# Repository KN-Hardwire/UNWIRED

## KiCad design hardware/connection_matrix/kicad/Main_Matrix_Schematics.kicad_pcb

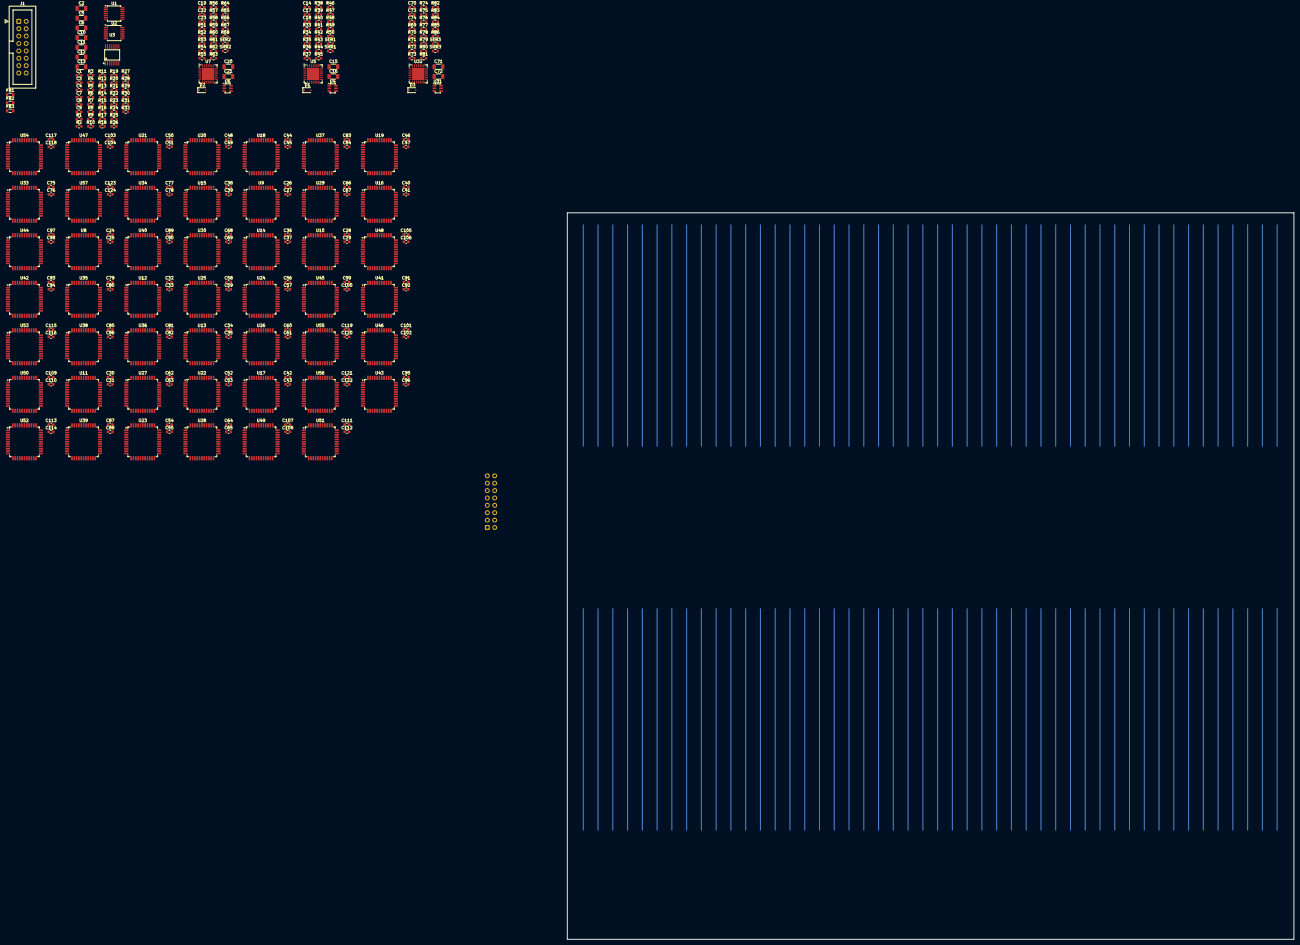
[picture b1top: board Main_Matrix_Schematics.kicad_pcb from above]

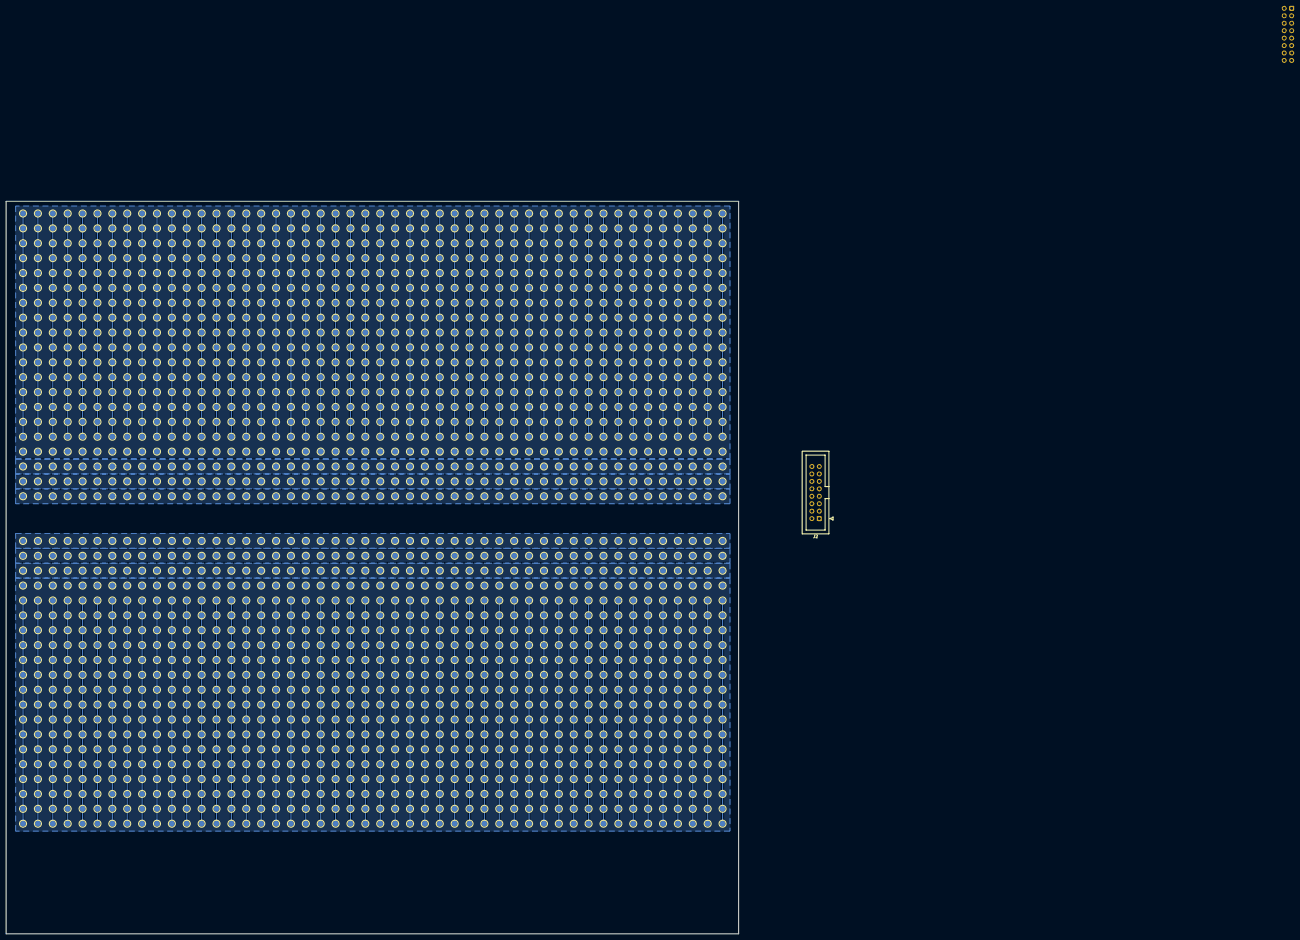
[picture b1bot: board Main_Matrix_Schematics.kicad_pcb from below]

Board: 4 copper layers, 250.0 x 250.0 mm, 2201 parts (1921 on the bottom side), 265 nets.

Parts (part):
+5P1, +5P1#2, +5P2, +5P2#2, +5P3, +5P3#2, +5P4, +5P4#2, +5P5, +5P5#2, +5P6, +5P6#2, +5P7, +5P7#2, +5P8, +5P8#2, +5P9, +5P9#2, +5P10, +5P10#2, +5P11, +5P11#2, +5P12, +5P12#2, +5P13, +5P13#2, +5P14, +5P14#2, +5P15, +5P15#2, +5P16, +5P16#2, +5P17, +5P17#2, +5P18, +5P18#2, +5P19, +5P19#2, +5P20, +5P20#2, +5P21, +5P21#2, +5P22, +5P22#2, +5P23, +5P23#2, +5P24, +5P24#2, +5P25, +5P25#2, +5P26, +5P26#2, +5P27, +5P27#2, +5P28, +5P28#2, +5P29, +5P29#2, +5P30, +5P30#2, +5P31, +5P31#2, +5P32, +5P32#2, +5P33, +5P33#2, +5P34, +5P34#2, +5P35, +5P35#2, +5P36, +5P36#2, +5P37, +5P37#2, +5P38, +5P38#2, +5P39, +5P39#2, +5P40, +5P40#2, +5P41, +5P41#2, +5P42, +5P42#2, +5P43, +5P43#2, +5P44, +5P44#2, +5P45, +5P45#2, +5P46, +5P46#2, +5P47, +5P47#2, +5P48, +5P48#2, +12P1, +12P1#2, +12P2, +12P2#2, +12P3, +12P3#2, +12P4, +12P4#2, +12P5, +12P5#2, +12P6, +12P6#2, +12P7, +12P7#2, +12P8, +12P8#2, +12P9, +12P9#2, +12P10, +12P10#2, +12P11, +12P11#2, +12P12, +12P12#2, +12P13, +12P13#2, +12P14, +12P14#2, +12P15, +12P15#2, +12P16, +12P16#2, +12P17, +12P17#2, +12P18, +12P18#2, +12P19, +12P19#2, +12P20, +12P20#2, +12P21, +12P21#2, +12P22, +12P22#2, +12P23, +12P23#2, +12P24, +12P24#2, +12P25, +12P25#2, +12P26, +12P26#2, +12P27, +12P27#2, +12P28, +12P28#2, +12P29, +12P29#2, +12P30, +12P30#2, +12P31, +12P31#2, +12P32, +12P32#2, +12P33, +12P33#2, +12P34, +12P34#2, +12P35, +12P35#2, +12P36, +12P36#2, +12P37, +12P37#2, +12P38, +12P38#2, +12P39, +12P39#2, +12P40, +12P40#2, +12P41, +12P41#2, +12P42, +12P42#2, +12P43, +12P43#2, +12P44, +12P44#2, +12P45, +12P45#2, +12P46, +12P46#2, +12P47, +12P47#2, +12P48, +12P48#2: Module_Pad; TestPoint_Pad_D2.0mm
-12P1, -12P1#2, -12P2, -12P2#2, -12P3, -12P3#2, -12P4, -12P4#2, -12P5, -12P5#2, -12P6, -12P6#2, -12P7, -12P7#2, -12P8, -12P8#2, -12P9, -12P9#2, -12P10, -12P10#2, -12P11, -12P11#2, -12P12, -12P12#2, -12P13, -12P13#2, -12P14, -12P14#2, -12P15, -12P15#2, -12P16, -12P16#2, -12P17, -12P17#2, -12P18, -12P18#2, -12P19, -12P19#2, -12P20, -12P20#2, -12P21, -12P21#2, -12P22, -12P22#2, -12P23, -12P23#2, -12P24, -12P24#2, -12P25, -12P25#2, -12P26, -12P26#2, -12P27, -12P27#2, -12P28, -12P28#2, -12P29, -12P29#2, -12P30, -12P30#2, -12P31, -12P31#2, -12P32, -12P32#2, -12P33, -12P33#2, -12P34, -12P34#2, -12P35, -12P35#2, -12P36, -12P36#2, -12P37, -12P37#2, -12P38, -12P38#2, -12P39, -12P39#2, -12P40, -12P40#2, -12P41, -12P41#2, -12P42, -12P42#2, -12P43, -12P43#2, -12P44, -12P44#2, -12P45, -12P45#2, -12P46, -12P46#2, -12P47, -12P47#2, -12P48, -12P48#2: Module_Pad; TestPoint_Pad_D2.0mm
C1, C3, C4, C7, C8, C9, C14, C17, C18, C19, C22, C23, C70, C73, C74: 100nF; C_0603_1608Metric
C2, C5, C6, C10, C11, C12, C13, C15, C16, C20, C21, C71, C72: 10uF; C_1206_3216Metric
C24, C25, C26, C27, C28, C29, C30, C31, C32, C33, C34, C35, C36, C37, C38, C39, C40, C41, C42, C43, C44, C45, C46, C47, C48, C49, C50, C51, C52, C53, C54, C55, C56, C57, C58, C59, C60, C61, C62, C63, C64, C65, C66, C67, C68, C69, C75, C76, C77, C78, C79, C80, C81, C82, C83, C84, C85, C86, C87, C88, C89, C90, C91, C92, C93, C94, C95, C96, C97, C98, C99, C100, C101, C102, C103, C104, C105, C106, C107, C108, C109, C110, C111, C112, C113, C114, C115, C116, C117, C118, C119, C120, C121, C122, C123, C124: 100n; C_0603_1608Metric
D1, D2, D3: BAT54J; D_SOD-323F
FB1, FB2, FB3: FerriteBead; L_0805_2012Metric
GNDP1, GNDP1#2, GNDP2, GNDP2#2, GNDP3, GNDP3#2, GNDP4, GNDP4#2, GNDP5, GNDP5#2, GNDP6, GNDP6#2, GNDP7, GNDP7#2, GNDP8, GNDP8#2, GNDP9, GNDP9#2, GNDP10, GNDP10#2, GNDP11, GNDP11#2, GNDP12, GNDP12#2, GNDP13, GNDP13#2, GNDP14, GNDP14#2, GNDP15, GNDP15#2, GNDP16, GNDP16#2, GNDP17, GNDP17#2, GNDP18, GNDP18#2, GNDP19, GNDP19#2, GNDP20, GNDP20#2, GNDP21, GNDP21#2, GNDP22, GNDP22#2, GNDP23, GNDP23#2, GNDP24, GNDP24#2, GNDP25, GNDP25#2, GNDP26, GNDP26#2, GNDP27, GNDP27#2, GNDP28, GNDP28#2, GNDP29, GNDP29#2, GNDP30, GNDP30#2, GNDP31, GNDP31#2, GNDP32, GNDP32#2, GNDP33, GNDP33#2, GNDP34, GNDP34#2, GNDP35, GNDP35#2, GNDP36, GNDP36#2, GNDP37, GNDP37#2, GNDP38, GNDP38#2, GNDP39, GNDP39#2, GNDP40, GNDP40#2, GNDP41, GNDP41#2, GNDP42, GNDP42#2, GNDP43, GNDP43#2, GNDP44, GNDP44#2, GNDP45, GNDP45#2, GNDP46, GNDP46#2, GNDP47, GNDP47#2, GNDP48, GNDP48#2: Module_Pad; TestPoint_Pad_D2.0mm
J1, J2: Conn_02x08_Odd_Even; IDC-Header_2x08_P2.54mm_Vertical
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
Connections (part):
+5V: C1.2, C2.1, C11.1, C14.1, C15.1, C17.1, C18.1, C19.1, C20.1, C22.1, C23.1, C24.2, C26.2, C28.2, C30.2, C32.2, C34.2, C36.2, C38.2, C40.2, C42.2, C44.2, C46.2, C48.2, C50.2, C52.2, C54.2, C56.2, C58.2, C60.2, C62.2, C64.2, C66.2, C68.2, C70.1, C71.1, C73.1, C74.1, C75.2, C77.2, C79.2, C81.2, C83.2, C85.2, C87.2, C89.2, C91.2, C93.2, C95.2, C97.2, C99.2, C101.2, C103.2, C105.2, C107.2, C109.2, C111.2, C113.2, C115.2, C117.2, C119.2, C121.2, C123.2, FB1.2, J1.5, SER1.1, SER2.1, SER3.1, U3.3 (AVDD), U3.9 (~CLR), U4.5 (VCC), U5.5 (V_{DD}), U6.5 (VCC), U7.5 (V_{DD}), U7.11 (A0), U8.38 (VDD), U9.38 (VDD), U10.38 (VDD), U11.38 (VDD), U12.38 (VDD)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
+12V: C3.2, C5.1, C7.1, C8.1, C10.1, FB2.2, J1.1, U1.4 (V+), U2.4 (V+)
-5V: C13.1, C16.1, C21.1, C25.2, C27.2, C29.2, C31.2, C33.2, C35.2, C37.2, C39.2, C41.2, C43.2, C45.2, C47.2, C49.2, C51.2, C53.2, C55.2, C57.2, C59.2, C61.2, C63.2, C65.2, C67.2, C69.2, C72.1, C76.2, C78.2, C80.2, C82.2, C84.2, C86.2, C88.2, C90.2, C92.2, C94.2, C96.2, C98.2, C100.2, C102.2, C104.2, C106.2, C108.2, C110.2, C112.2, C114.2, C116.2, C118.2, C120.2, C122.2, C124.2, J1.7, U8.16 (VEE), U9.16 (VEE), U10.16 (VEE), U11.16 (VEE), U12.16 (VEE), U13.16 (VEE), U14.16 (VEE), U15.16 (VEE), U16.16 (VEE), U17.16 (VEE), U18.16 (VEE), U19.16 (VEE), U20.16 (VEE), U21.16 (VEE), U22.16 (VEE), U23.16 (VEE), U24.16 (VEE), U25.16 (VEE), U26.16 (VEE), U27.16 (VEE), U28.16 (VEE), U29.16 (VEE), U30.16 (VEE), U33.16 (VEE), U34.16 (VEE), U35.16 (VEE), U36.16 (VEE)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
-12V: C4.2, C6.1, C7.2, C8.2, C12.1, FB3.1, J1.3, U1.11 (V-), U2.11 (V-)
/+5_OUT: +5P1.1 (1_1), +5P1#2.1 (1_1), +5P2.1 (1_1), +5P2#2.1 (1_1), +5P3.1 (1_1), +5P3#2.1 (1_1), +5P4.1 (1_1), +5P4#2.1 (1_1), +5P5.1 (1_1), +5P5#2.1 (1_1), +5P6.1 (1_1), +5P6#2.1 (1_1), +5P7.1 (1_1), +5P7#2.1 (1_1), +5P8.1 (1_1), +5P8#2.1 (1_1), +5P9.1 (1_1), +5P9#2.1 (1_1), +5P10.1 (1_1), +5P10#2.1 (1_1), +5P11.1 (1_1), +5P11#2.1 (1_1), +5P12.1 (1_1), +5P12#2.1 (1_1), +5P13.1 (1_1), +5P13#2.1 (1_1), +5P14.1 (1_1), +5P14#2.1 (1_1), +5P15.1 (1_1), +5P15#2.1 (1_1), +5P16.1 (1_1), +5P16#2.1 (1_1), +5P17.1 (1_1), +5P17#2.1 (1_1), +5P18.1 (1_1), +5P18#2.1 (1_1), +5P19.1 (1_1), +5P19#2.1 (1_1), +5P20.1 (1_1), +5P20#2.1 (1_1), +5P21.1 (1_1), +5P21#2.1 (1_1), +5P22.1 (1_1), +5P22#2.1 (1_1), +5P23.1 (1_1), +5P23#2.1 (1_1), +5P24.1 (1_1), +5P24#2.1 (1_1), +5P25.1 (1_1), +5P25#2.1 (1_1), +5P26.1 (1_1), +5P26#2.1 (1_1), +5P27.1 (1_1), +5P27#2.1 (1_1), +5P28.1 (1_1), +5P28#2.1 (1_1), +5P29.1 (1_1), +5P29#2.1 (1_1), +5P30.1 (1_1), +5P30#2.1 (1_1), +5P31.1 (1_1), +5P31#2.1 (1_1), +5P32.1 (1_1), +5P32#2.1 (1_1), +5P33.1 (1_1), +5P33#2.1 (1_1), +5P34.1 (1_1), +5P34#2.1 (1_1), +5P35.1 (1_1), +5P35#2.1 (1_1), +5P36.1 (1_1), +5P36#2.1 (1_1), +5P37.1 (1_1), +5P37#2.1 (1_1), +5P38.1 (1_1), +5P38#2.1 (1_1), +5P39.1 (1_1), +5P39#2.1 (1_1), +5P40.1 (1_1), +5P40#2.1 (1_1)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
/+12_OUT: +12P1.1 (1_1), +12P1#2.1 (1_1), +12P2.1 (1_1), +12P2#2.1 (1_1), +12P3.1 (1_1), +12P3#2.1 (1_1), +12P4.1 (1_1), +12P4#2.1 (1_1), +12P5.1 (1_1), +12P5#2.1 (1_1), +12P6.1 (1_1), +12P6#2.1 (1_1), +12P7.1 (1_1), +12P7#2.1 (1_1), +12P8.1 (1_1), +12P8#2.1 (1_1), +12P9.1 (1_1), +12P9#2.1 (1_1), +12P10.1 (1_1), +12P10#2.1 (1_1), +12P11.1 (1_1), +12P11#2.1 (1_1), +12P12.1 (1_1), +12P12#2.1 (1_1), +12P13.1 (1_1), +12P13#2.1 (1_1), +12P14.1 (1_1), +12P14#2.1 (1_1), +12P15.1 (1_1), +12P15#2.1 (1_1), +12P16.1 (1_1), +12P16#2.1 (1_1), +12P17.1 (1_1), +12P17#2.1 (1_1), +12P18.1 (1_1), +12P18#2.1 (1_1), +12P19.1 (1_1), +12P19#2.1 (1_1), +12P20.1 (1_1), +12P20#2.1 (1_1), +12P21.1 (1_1), +12P21#2.1 (1_1), +12P22.1 (1_1), +12P22#2.1 (1_1), +12P23.1 (1_1), +12P23#2.1 (1_1), +12P24.1 (1_1), +12P24#2.1 (1_1), +12P25.1 (1_1), +12P25#2.1 (1_1), +12P26.1 (1_1), +12P26#2.1 (1_1), +12P27.1 (1_1), +12P27#2.1 (1_1), +12P28.1 (1_1), +12P28#2.1 (1_1), +12P29.1 (1_1), +12P29#2.1 (1_1), +12P30.1 (1_1), +12P30#2.1 (1_1), +12P31.1 (1_1), +12P31#2.1 (1_1), +12P32.1 (1_1), +12P32#2.1 (1_1), +12P33.1 (1_1), +12P33#2.1 (1_1), +12P34.1 (1_1), +12P34#2.1 (1_1), +12P35.1 (1_1), +12P35#2.1 (1_1), +12P36.1 (1_1), +12P36#2.1 (1_1), +12P37.1 (1_1), +12P37#2.1 (1_1), +12P38.1 (1_1), +12P38#2.1 (1_1), +12P39.1 (1_1), +12P39#2.1 (1_1), +12P40.1 (1_1), +12P40#2.1 (1_1)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
/-12_OUT: -12P1.1 (1_1), -12P1#2.1 (1_1), -12P2.1 (1_1), -12P2#2.1 (1_1), -12P3.1 (1_1), -12P3#2.1 (1_1), -12P4.1 (1_1), -12P4#2.1 (1_1), -12P5.1 (1_1), -12P5#2.1 (1_1), -12P6.1 (1_1), -12P6#2.1 (1_1), -12P7.1 (1_1), -12P7#2.1 (1_1), -12P8.1 (1_1), -12P8#2.1 (1_1), -12P9.1 (1_1), -12P9#2.1 (1_1), -12P10.1 (1_1), -12P10#2.1 (1_1), -12P11.1 (1_1), -12P11#2.1 (1_1), -12P12.1 (1_1), -12P12#2.1 (1_1), -12P13.1 (1_1), -12P13#2.1 (1_1), -12P14.1 (1_1), -12P14#2.1 (1_1), -12P15.1 (1_1), -12P15#2.1 (1_1), -12P16.1 (1_1), -12P16#2.1 (1_1), -12P17.1 (1_1), -12P17#2.1 (1_1), -12P18.1 (1_1), -12P18#2.1 (1_1), -12P19.1 (1_1), -12P19#2.1 (1_1), -12P20.1 (1_1), -12P20#2.1 (1_1), -12P21.1 (1_1), -12P21#2.1 (1_1), -12P22.1 (1_1), -12P22#2.1 (1_1), -12P23.1 (1_1), -12P23#2.1 (1_1), -12P24.1 (1_1), -12P24#2.1 (1_1), -12P25.1 (1_1), -12P25#2.1 (1_1), -12P26.1 (1_1), -12P26#2.1 (1_1), -12P27.1 (1_1), -12P27#2.1 (1_1), -12P28.1 (1_1), -12P28#2.1 (1_1), -12P29.1 (1_1), -12P29#2.1 (1_1), -12P30.1 (1_1), -12P30#2.1 (1_1), -12P31.1 (1_1), -12P31#2.1 (1_1), -12P32.1 (1_1), -12P32#2.1 (1_1), -12P33.1 (1_1), -12P33#2.1 (1_1), -12P34.1 (1_1), -12P34#2.1 (1_1), -12P35.1 (1_1), -12P35#2.1 (1_1), -12P36.1 (1_1), -12P36#2.1 (1_1), -12P37.1 (1_1), -12P37#2.1 (1_1), -12P38.1 (1_1), -12P38#2.1 (1_1), -12P39.1 (1_1), -12P39#2.1 (1_1), -12P40.1 (1_1), -12P40#2.1 (1_1)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
/AUX_BUS0: R7.2, U27.31 (X0), U28.31 (X0), U29.31 (X0), U30.31 (X0), U37.31 (X0), U38.31 (X0), U39.31 (X0), U40.31 (X0), U53.31 (X0), U54.31 (X0), U55.31 (X0), U56.31 (X0)
/AUX_BUS1: R8.2, U27.30 (X1), U28.30 (X1), U29.30 (X1), U30.30 (X1), U37.30 (X1), U38.30 (X1), U39.30 (X1), U40.30 (X1), U53.30 (X1), U54.30 (X1), U55.30 (X1), U56.30 (X1)
/AUX_BUS2: R15.2, U27.29 (X2), U28.29 (X2), U29.29 (X2), U30.29 (X2), U37.29 (X2), U38.29 (X2), U39.29 (X2), U40.29 (X2), U53.29 (X2), U54.29 (X2), U55.29 (X2), U56.29 (X2)
/AUX_BUS3: R16.2, U27.28 (X3), U28.28 (X3), U29.28 (X3), U30.28 (X3), U37.28 (X3), U38.28 (X3), U39.28 (X3), U40.28 (X3), U53.28 (X3), U54.28 (X3), U55.28 (X3), U56.28 (X3)
/AUX_BUS4: R23.2, U27.27 (X4), U28.27 (X4), U29.27 (X4), U30.27 (X4), U37.27 (X4), U38.27 (X4), U39.27 (X4), U40.27 (X4), U53.27 (X4), U54.27 (X4), U55.27 (X4), U56.27 (X4)
/AUX_BUS5: R24.2, U27.26 (X5), U28.26 (X5), U29.26 (X5), U30.26 (X5), U37.26 (X5), U38.26 (X5), U39.26 (X5), U40.26 (X5), U53.26 (X5), U54.26 (X5), U55.26 (X5), U56.26 (X5)
/AUX_BUS6: R31.2, U27.3 (X6), U28.3 (X6), U29.3 (X6), U30.3 (X6), U37.3 (X6), U38.3 (X6), U39.3 (X6), U40.3 (X6), U53.3 (X6), U54.3 (X6), U55.3 (X6), U56.3 (X6)
/AUX_BUS7: R32.2, U27.4 (X7), U28.4 (X7), U29.4 (X7), U30.4 (X7), U37.4 (X7), U38.4 (X7), U39.4 (X7), U40.4 (X7), U53.4 (X7), U54.4 (X7), U55.4 (X7), U56.4 (X7)
/AUX_BUS8: J2.1, U27.5 (X8), U28.5 (X8), U29.5 (X8), U30.5 (X8), U37.5 (X8), U38.5 (X8), U39.5 (X8), U40.5 (X8), U53.5 (X8), U54.5 (X8), U55.5 (X8), U56.5 (X8)
/AUX_BUS9: J2.3, U27.6 (X9), U28.6 (X9), U29.6 (X9), U30.6 (X9), U37.6 (X9), U38.6 (X9), U39.6 (X9), U40.6 (X9), U53.6 (X9), U54.6 (X9), U55.6 (X9), U56.6 (X9)
/AUX_BUS10: J2.5, U27.7 (X10), U28.7 (X10), U29.7 (X10), U30.7 (X10), U37.7 (X10), U38.7 (X10), U39.7 (X10), U40.7 (X10), U53.7 (X10), U54.7 (X10), U55.7 (X10), U56.7 (X10)
/AUX_BUS11: J2.7, U27.8 (X11), U28.8 (X11), U29.8 (X11), U30.8 (X11), U37.8 (X11), U38.8 (X11), U39.8 (X11), U40.8 (X11), U53.8 (X11), U54.8 (X11), U55.8 (X11), U56.8 (X11)
/AUX_BUS12: J2.9, U27.25 (X12), U28.25 (X12), U29.25 (X12), U30.25 (X12), U37.25 (X12), U38.25 (X12), U39.25 (X12), U40.25 (X12), U53.25 (X12), U54.25 (X12), U55.25 (X12), U56.25 (X12)
/AUX_BUS13: J2.11, U27.24 (X13), U28.24 (X13), U29.24 (X13), U30.24 (X13), U37.24 (X13), U38.24 (X13), U39.24 (X13), U40.24 (X13), U53.24 (X13), U54.24 (X13), U55.24 (X13), U56.24 (X13)
/AUX_BUS14: J2.13, U27.1 (X14), U28.1 (X14), U29.1 (X14), U30.1 (X14), U37.1 (X14), U38.1 (X14), U39.1 (X14), U40.1 (X14), U53.1 (X14), U54.1 (X14), U55.1 (X14), U56.1 (X14)
/AUX_BUS15: J2.15, U27.2 (X15), U28.2 (X15), U29.2 (X15), U30.2 (X15), U37.2 (X15), U38.2 (X15), U39.2 (X15), U40.2 (X15), U53.2 (X15), U54.2 (X15), U55.2 (X15), U56.2 (X15)
/DAC_A: U1.3 (+), U3.4 (VOUTA)
/DAC_B: U1.5 (+), U3.13 (VOUTB)
/DAC_C: U1.10 (+), U3.5 (VOUTC)
/DAC_D: U1.12 (+), U3.12 (VOUTD)
/DAC_E: U2.3 (+), U3.6 (VOUTE)
/DAC_F: U2.5 (+), U3.11 (VOUTF)
/DAC_G: U2.10 (+), U3.7 (VOUTG)
/DAC_H: U2.12 (+), U3.10 (VOUTH)
/SPI.CS1: J1.9, U5.7 (~CS), U7.7 (~CS), U32.7 (~CS)
/SPI.CS2: J1.10, U3.2 (~SYNC)
/SPI.MOSI: J1.13, U3.15 (DIN), U5.9 (SI), U7.9 (SI), U32.9 (SI)
/SPI.SCK: J1.11, U3.16 (SCLK), U5.8 (SCK), U7.8 (SCK), U32.8 (SCK)
/Sector1/CBUS10: U8.31 (X0), U11.31 (X0), U12.31 (X0), U15.31 (X0), U16.31 (X0), U23.31 (X0), U24.31 (X0), U45.31 (X0), U46.31 (X0), U49.31 (X0), U50.31 (X0), U57.31 (X0)
/Sector1/CBUS11: U8.30 (X1), U11.30 (X1), U12.30 (X1), U15.30 (X1), U16.30 (X1), U23.30 (X1), U24.30 (X1), U45.30 (X1), U46.30 (X1), U49.30 (X1), U50.30 (X1), U57.30 (X1)
/Sector1/CBUS12: U8.29 (X2), U11.29 (X2), U12.29 (X2), U15.29 (X2), U16.29 (X2), U23.29 (X2), U24.29 (X2), U45.29 (X2), U46.29 (X2), U49.29 (X2), U50.29 (X2), U57.29 (X2)
/Sector1/CBUS13: U8.28 (X3), U11.28 (X3), U12.28 (X3), U15.28 (X3), U16.28 (X3), U23.28 (X3), U24.28 (X3), U45.28 (X3), U46.28 (X3), U49.28 (X3), U50.28 (X3), U57.28 (X3)
/Sector1/CBUS14: U8.27 (X4), U11.27 (X4), U12.27 (X4), U15.27 (X4), U16.27 (X4), U23.27 (X4), U24.27 (X4), U45.27 (X4), U46.27 (X4), U49.27 (X4), U50.27 (X4), U57.27 (X4)
/Sector1/CBUS15: U8.26 (X5), U11.26 (X5), U12.26 (X5), U15.26 (X5), U16.26 (X5), U23.26 (X5), U24.26 (X5), U45.26 (X5), U46.26 (X5), U49.26 (X5), U50.26 (X5), U57.26 (X5)
/Sector1/CBUS16: U8.3 (X6), U11.3 (X6), U12.3 (X6), U15.3 (X6), U16.3 (X6), U23.3 (X6), U24.3 (X6), U45.3 (X6), U46.3 (X6), U49.3 (X6), U50.3 (X6), U57.3 (X6)
/Sector1/CBUS17: U8.4 (X7), U11.4 (X7), U12.4 (X7), U15.4 (X7), U16.4 (X7), U23.4 (X7), U24.4 (X7), U45.4 (X7), U46.4 (X7), U49.4 (X7), U50.4 (X7), U57.4 (X7)
/Sector1/CBUS18: U8.5 (X8), U11.5 (X8), U12.5 (X8), U15.5 (X8), U16.5 (X8), U23.5 (X8), U24.5 (X8), U45.5 (X8), U46.5 (X8), U49.5 (X8), U50.5 (X8), U57.5 (X8)
/Sector1/CBUS19: U8.6 (X9), U11.6 (X9), U12.6 (X9), U15.6 (X9), U16.6 (X9), U23.6 (X9), U24.6 (X9), U45.6 (X9), U46.6 (X9), U49.6 (X9), U50.6 (X9), U57.6 (X9)
/Sector1/CBUS20: U13.31 (X0), U14.31 (X0), U18.31 (X0), U19.31 (X0), U20.31 (X0), U21.31 (X0), U22.31 (X0), U25.31 (X0), U43.31 (X0), U44.31 (X0), U48.31 (X0), U51.31 (X0)
/Sector1/CBUS21: U13.30 (X1), U14.30 (X1), U18.30 (X1), U19.30 (X1), U20.30 (X1), U21.30 (X1), U22.30 (X1), U25.30 (X1), U43.30 (X1), U44.30 (X1), U48.30 (X1), U51.30 (X1)
/Sector1/CBUS22: U13.29 (X2), U14.29 (X2), U18.29 (X2), U19.29 (X2), U20.29 (X2), U21.29 (X2), U22.29 (X2), U25.29 (X2), U43.29 (X2), U44.29 (X2), U48.29 (X2), U51.29 (X2)
/Sector1/CBUS23: U13.28 (X3), U14.28 (X3), U18.28 (X3), U19.28 (X3), U20.28 (X3), U21.28 (X3), U22.28 (X3), U25.28 (X3), U43.28 (X3), U44.28 (X3), U48.28 (X3), U51.28 (X3)
/Sector1/CBUS24: U13.27 (X4), U14.27 (X4), U18.27 (X4), U19.27 (X4), U20.27 (X4), U21.27 (X4), U22.27 (X4), U25.27 (X4), U43.27 (X4), U44.27 (X4), U48.27 (X4), U51.27 (X4)
/Sector1/CBUS25: U13.26 (X5), U14.26 (X5), U18.26 (X5), U19.26 (X5), U20.26 (X5), U21.26 (X5), U22.26 (X5), U25.26 (X5), U43.26 (X5), U44.26 (X5), U48.26 (X5), U51.26 (X5)
/Sector1/CBUS26: U13.3 (X6), U14.3 (X6), U18.3 (X6), U19.3 (X6), U20.3 (X6), U21.3 (X6), U22.3 (X6), U25.3 (X6), U43.3 (X6), U44.3 (X6), U48.3 (X6), U51.3 (X6)
/Sector1/CBUS27: U13.4 (X7), U14.4 (X7), U18.4 (X7), U19.4 (X7), U20.4 (X7), U21.4 (X7), U22.4 (X7), U25.4 (X7), U43.4 (X7), U44.4 (X7), U48.4 (X7), U51.4 (X7)
/Sector1/CBUS28: U13.5 (X8), U14.5 (X8), U18.5 (X8), U19.5 (X8), U20.5 (X8), U21.5 (X8), U22.5 (X8), U25.5 (X8), U43.5 (X8), U44.5 (X8), U48.5 (X8), U51.5 (X8)
/Sector1/CBUS29: U13.6 (X9), U14.6 (X9), U18.6 (X9), U19.6 (X9), U20.6 (X9), U21.6 (X9), U22.6 (X9), U25.6 (X9), U43.6 (X9), U44.6 (X9), U48.6 (X9), U51.6 (X9)
/Sector1/CBUS30: U9.31 (X0), U10.31 (X0), U17.31 (X0), U26.31 (X0), U33.31 (X0), U34.31 (X0), U35.31 (X0), U36.31 (X0), U41.31 (X0), U42.31 (X0), U47.31 (X0), U52.31 (X0)
/Sector1/CBUS31: U9.30 (X1), U10.30 (X1), U17.30 (X1), U26.30 (X1), U33.30 (X1), U34.30 (X1), U35.30 (X1), U36.30 (X1), U41.30 (X1), U42.30 (X1), U47.30 (X1), U52.30 (X1)
/Sector1/CBUS32: U9.29 (X2), U10.29 (X2), U17.29 (X2), U26.29 (X2), U33.29 (X2), U34.29 (X2), U35.29 (X2), U36.29 (X2), U41.29 (X2), U42.29 (X2), U47.29 (X2), U52.29 (X2)
/Sector1/CBUS33: U9.28 (X3), U10.28 (X3), U17.28 (X3), U26.28 (X3), U33.28 (X3), U34.28 (X3), U35.28 (X3), U36.28 (X3), U41.28 (X3), U42.28 (X3), U47.28 (X3), U52.28 (X3)
/Sector1/CBUS34: U9.27 (X4), U10.27 (X4), U17.27 (X4), U26.27 (X4), U33.27 (X4), U34.27 (X4), U35.27 (X4), U36.27 (X4), U41.27 (X4), U42.27 (X4), U47.27 (X4), U52.27 (X4)
/Sector1/CBUS35: U9.26 (X5), U10.26 (X5), U17.26 (X5), U26.26 (X5), U33.26 (X5), U34.26 (X5), U35.26 (X5), U36.26 (X5), U41.26 (X5), U42.26 (X5), U47.26 (X5), U52.26 (X5)
/Sector1/CBUS36: U9.3 (X6), U10.3 (X6), U17.3 (X6), U26.3 (X6), U33.3 (X6), U34.3 (X6), U35.3 (X6), U36.3 (X6), U41.3 (X6), U42.3 (X6), U47.3 (X6), U52.3 (X6)
/Sector1/CBUS37: U9.4 (X7), U10.4 (X7), U17.4 (X7), U26.4 (X7), U33.4 (X7), U34.4 (X7), U35.4 (X7), U36.4 (X7), U41.4 (X7), U42.4 (X7), U47.4 (X7), U52.4 (X7)
/Sector1/CBUS38: U9.5 (X8), U10.5 (X8), U17.5 (X8), U26.5 (X8), U33.5 (X8), U34.5 (X8), U35.5 (X8), U36.5 (X8), U41.5 (X8), U42.5 (X8), U47.5 (X8), U52.5 (X8)
/Sector1/CBUS39: U9.6 (X9), U10.6 (X9), U17.6 (X9), U26.6 (X9), U33.6 (X9), U34.6 (X9), U35.6 (X9), U36.6 (X9), U41.6 (X9), U42.6 (X9), U47.6 (X9), U52.6 (X9)
/Sector1/CBUS110: U8.7 (X10), U11.7 (X10), U12.7 (X10), U15.7 (X10), U16.7 (X10), U23.7 (X10), U24.7 (X10), U45.7 (X10), U46.7 (X10), U49.7 (X10), U50.7 (X10), U57.7 (X10)
/Sector1/CBUS111: U8.8 (X11), U11.8 (X11), U12.8 (X11), U15.8 (X11), U16.8 (X11), U23.8 (X11), U24.8 (X11), U45.8 (X11), U46.8 (X11), U49.8 (X11), U50.8 (X11), U57.8 (X11)
/Sector1/CBUS112: U8.25 (X12), U11.25 (X12), U12.25 (X12), U15.25 (X12), U16.25 (X12), U23.25 (X12), U24.25 (X12), U45.25 (X12), U46.25 (X12), U49.25 (X12), U50.25 (X12), U57.25 (X12)
/Sector1/CBUS113: U8.24 (X13), U11.24 (X13), U12.24 (X13), U15.24 (X13), U16.24 (X13), U23.24 (X13), U24.24 (X13), U45.24 (X13), U46.24 (X13), U49.24 (X13), U50.24 (X13), U57.24 (X13)
/Sector1/CBUS114: U8.1 (X14), U11.1 (X14), U12.1 (X14), U15.1 (X14), U16.1 (X14), U23.1 (X14), U24.1 (X14), U45.1 (X14), U46.1 (X14), U49.1 (X14), U50.1 (X14), U57.1 (X14)
/Sector1/CBUS115: U8.2 (X15), U11.2 (X15), U12.2 (X15), U15.2 (X15), U16.2 (X15), U23.2 (X15), U24.2 (X15), U45.2 (X15), U46.2 (X15), U49.2 (X15), U50.2 (X15), U57.2 (X15)
/Sector1/CBUS210: U13.7 (X10), U14.7 (X10), U18.7 (X10), U19.7 (X10), U20.7 (X10), U21.7 (X10), U22.7 (X10), U25.7 (X10), U43.7 (X10), U44.7 (X10), U48.7 (X10), U51.7 (X10)
/Sector1/CBUS211: U13.8 (X11), U14.8 (X11), U18.8 (X11), U19.8 (X11), U20.8 (X11), U21.8 (X11), U22.8 (X11), U25.8 (X11), U43.8 (X11), U44.8 (X11), U48.8 (X11), U51.8 (X11)
/Sector1/CBUS212: U13.25 (X12), U14.25 (X12), U18.25 (X12), U19.25 (X12), U20.25 (X12), U21.25 (X12), U22.25 (X12), U25.25 (X12), U43.25 (X12), U44.25 (X12), U48.25 (X12), U51.25 (X12)
/Sector1/CBUS213: U13.24 (X13), U14.24 (X13), U18.24 (X13), U19.24 (X13), U20.24 (X13), U21.24 (X13), U22.24 (X13), U25.24 (X13), U43.24 (X13), U44.24 (X13), U48.24 (X13), U51.24 (X13)
/Sector1/CBUS214: U13.1 (X14), U14.1 (X14), U18.1 (X14), U19.1 (X14), U20.1 (X14), U21.1 (X14), U22.1 (X14), U25.1 (X14), U43.1 (X14), U44.1 (X14), U48.1 (X14), U51.1 (X14)
/Sector1/CBUS215: U13.2 (X15), U14.2 (X15), U18.2 (X15), U19.2 (X15), U20.2 (X15), U21.2 (X15), U22.2 (X15), U25.2 (X15), U43.2 (X15), U44.2 (X15), U48.2 (X15), U51.2 (X15)
/Sector1/CBUS310: U9.7 (X10), U10.7 (X10), U17.7 (X10), U26.7 (X10), U33.7 (X10), U34.7 (X10), U35.7 (X10), U36.7 (X10), U41.7 (X10), U42.7 (X10), U47.7 (X10), U52.7 (X10)
/Sector1/CBUS311: U9.8 (X11), U10.8 (X11), U17.8 (X11), U26.8 (X11), U33.8 (X11), U34.8 (X11), U35.8 (X11), U36.8 (X11), U41.8 (X11), U42.8 (X11), U47.8 (X11), U52.8 (X11)
/Sector1/CBUS312: U9.25 (X12), U10.25 (X12), U17.25 (X12), U26.25 (X12), U33.25 (X12), U34.25 (X12), U35.25 (X12), U36.25 (X12), U41.25 (X12), U42.25 (X12), U47.25 (X12), U52.25 (X12)
/Sector1/CBUS313: U9.24 (X13), U10.24 (X13), U17.24 (X13), U26.24 (X13), U33.24 (X13), U34.24 (X13), U35.24 (X13), U36.24 (X13), U41.24 (X13), U42.24 (X13), U47.24 (X13), U52.24 (X13)
/Sector1/CBUS314: U9.1 (X14), U10.1 (X14), U17.1 (X14), U26.1 (X14), U33.1 (X14), U34.1 (X14), U35.1 (X14), U36.1 (X14), U41.1 (X14), U42.1 (X14), U47.1 (X14), U52.1 (X14)
/Sector1/CBUS315: U9.2 (X15), U10.2 (X15), U17.2 (X15), U26.2 (X15), U33.2 (X15), U34.2 (X15), U35.2 (X15), U36.2 (X15), U41.2 (X15), U42.2 (X15), U47.2 (X15), U52.2 (X15)
/Sector1/CH_CTR.CLK: J1.15, U4.1, U6.1, U31.1
/Sector1/CH_CTR.DAT: J1.14, U4.3, U6.3, U31.3
/Sector1/CLK: R33.2, U8.34 (CS/CK), U11.34 (CS/CK), U12.34 (CS/CK), U18.34 (CS/CK), U19.34 (CS/CK), U20.34 (CS/CK), U21.34 (CS/CK), U33.34 (CS/CK), U34.34 (CS/CK), U35.34 (CS/CK), U36.34 (CS/CK), U37.34 (CS/CK), U38.34 (CS/CK), U39.34 (CS/CK), U40.34 (CS/CK), U57.34 (CS/CK)
/Sector1/DAT: R34.2, U8.36 (DAT), U11.36 (DAT), U12.36 (DAT), U18.36 (DAT), U19.36 (DAT), U20.36 (DAT), U21.36 (DAT), U33.36 (DAT), U34.36 (DAT), U35.36 (DAT), U36.36 (DAT), U37.36 (DAT), U38.36 (DAT), U39.36 (DAT), U40.36 (DAT), U57.36 (DAT)
/Sector1/MP1_0: MP1.1 (1_1), MP1#2.1 (1_1), MP97.1 (1_1), MP145.1 (1_1), MP193.1 (1_1), MP241.1 (1_1), MP289.1 (1_1), MP337.1 (1_1), MP385.1 (1_1), MP433.1 (1_1), MP481.1 (1_1), MP529.1 (1_1), MP577.1 (1_1), MP625.1 (1_1), MP673.1 (1_1), MP769.1 (1_1), U18.33 (Y0), U33.33 (Y0), U37.33 (Y0), U57.33 (Y0)
/Sector1/MP1_1: MP2.1 (1_1), MP2#2.1 (1_1), MP98.1 (1_1), MP146.1 (1_1), MP194.1 (1_1), MP242.1 (1_1), MP290.1 (1_1), MP338.1 (1_1), MP386.1 (1_1), MP434.1 (1_1), MP482.1 (1_1), MP530.1 (1_1), MP578.1 (1_1), MP626.1 (1_1), MP674.1 (1_1), MP770.1 (1_1), U18.35 (Y1), U33.35 (Y1), U37.35 (Y1), U57.35 (Y1)
/Sector1/MP1_2: MP3.1 (1_1), MP3#2.1 (1_1), MP99.1 (1_1), MP147.1 (1_1), MP195.1 (1_1), MP243.1 (1_1), MP291.1 (1_1), MP339.1 (1_1), MP387.1 (1_1), MP435.1 (1_1), MP483.1 (1_1), MP531.1 (1_1), MP579.1 (1_1), MP627.1 (1_1), MP675.1 (1_1), MP771.1 (1_1), U18.37 (Y2), U33.37 (Y2), U37.37 (Y2), U57.37 (Y2)
/Sector1/MP1_3: MP4.1 (1_1), MP4#2.1 (1_1), MP100.1 (1_1), MP148.1 (1_1), MP196.1 (1_1), MP244.1 (1_1), MP292.1 (1_1), MP340.1 (1_1), MP388.1 (1_1), MP436.1 (1_1), MP484.1 (1_1), MP532.1 (1_1), MP580.1 (1_1), MP628.1 (1_1), MP676.1 (1_1), MP772.1 (1_1), U18.39 (Y3), U33.39 (Y3), U37.39 (Y3), U57.39 (Y3)
/Sector1/MP1_4: MP5.1 (1_1), MP5#2.1 (1_1), MP101.1 (1_1), MP149.1 (1_1), MP197.1 (1_1), MP245.1 (1_1), MP293.1 (1_1), MP341.1 (1_1), MP389.1 (1_1), MP437.1 (1_1), MP485.1 (1_1), MP533.1 (1_1), MP581.1 (1_1), MP629.1 (1_1), MP677.1 (1_1), MP773.1 (1_1), U18.17 (Y4), U33.17 (Y4), U37.17 (Y4), U57.17 (Y4)
/Sector1/MP1_5: MP6.1 (1_1), MP6#2.1 (1_1), MP102.1 (1_1), MP150.1 (1_1), MP198.1 (1_1), MP246.1 (1_1), MP294.1 (1_1), MP342.1 (1_1), MP390.1 (1_1), MP438.1 (1_1), MP486.1 (1_1), MP534.1 (1_1), MP582.1 (1_1), MP630.1 (1_1), MP678.1 (1_1), MP774.1 (1_1), U18.15 (Y5), U33.15 (Y5), U37.15 (Y5), U57.15 (Y5)
/Sector1/MP1_6: MP7.1 (1_1), MP7#2.1 (1_1), MP103.1 (1_1), MP151.1 (1_1), MP199.1 (1_1), MP247.1 (1_1), MP295.1 (1_1), MP343.1 (1_1), MP391.1 (1_1), MP439.1 (1_1), MP487.1 (1_1), MP535.1 (1_1), MP583.1 (1_1), MP631.1 (1_1), MP679.1 (1_1), MP775.1 (1_1), U18.13 (Y6), U33.13 (Y6), U37.13 (Y6), U57.13 (Y6)
/Sector1/MP1_7: MP8.1 (1_1), MP8#2.1 (1_1), MP104.1 (1_1), MP152.1 (1_1), MP200.1 (1_1), MP248.1 (1_1), MP296.1 (1_1), MP344.1 (1_1), MP392.1 (1_1), MP440.1 (1_1), MP488.1 (1_1), MP536.1 (1_1), MP584.1 (1_1), MP632.1 (1_1), MP680.1 (1_1), MP776.1 (1_1), U18.11 (Y7), U33.11 (Y7), U37.11 (Y7), U57.11 (Y7)
/Sector1/MP2_0: MP9.1 (1_1), MP9#2.1 (1_1), MP105.1 (1_1), MP153.1 (1_1), MP201.1 (1_1), MP249.1 (1_1), MP297.1 (1_1), MP345.1 (1_1), MP393.1 (1_1), MP441.1 (1_1), MP489.1 (1_1), MP537.1 (1_1), MP585.1 (1_1), MP633.1 (1_1), MP681.1 (1_1), MP777.1 (1_1), U8.33 (Y0), U19.33 (Y0), U34.33 (Y0), U38.33 (Y0)
/Sector1/MP2_1: MP10.1 (1_1), MP10#2.1 (1_1), MP106.1 (1_1), MP154.1 (1_1), MP202.1 (1_1), MP250.1 (1_1), MP298.1 (1_1), MP346.1 (1_1), MP394.1 (1_1), MP442.1 (1_1), MP490.1 (1_1), MP538.1 (1_1), MP586.1 (1_1), MP634.1 (1_1), MP682.1 (1_1), MP778.1 (1_1), U8.35 (Y1), U19.35 (Y1), U34.35 (Y1), U38.35 (Y1)
/Sector1/MP2_2: MP11.1 (1_1), MP11#2.1 (1_1), MP107.1 (1_1), MP155.1 (1_1), MP203.1 (1_1), MP251.1 (1_1), MP299.1 (1_1), MP347.1 (1_1), MP395.1 (1_1), MP443.1 (1_1), MP491.1 (1_1), MP539.1 (1_1), MP587.1 (1_1), MP635.1 (1_1), MP683.1 (1_1), MP779.1 (1_1), U8.37 (Y2), U19.37 (Y2), U34.37 (Y2), U38.37 (Y2)
/Sector1/MP2_3: MP12.1 (1_1), MP12#2.1 (1_1), MP108.1 (1_1), MP156.1 (1_1), MP204.1 (1_1), MP252.1 (1_1), MP300.1 (1_1), MP348.1 (1_1), MP396.1 (1_1), MP444.1 (1_1), MP492.1 (1_1), MP540.1 (1_1), MP588.1 (1_1), MP636.1 (1_1), MP684.1 (1_1), MP780.1 (1_1), U8.39 (Y3), U19.39 (Y3), U34.39 (Y3), U38.39 (Y3)
/Sector1/MP2_4: MP13.1 (1_1), MP13#2.1 (1_1), MP109.1 (1_1), MP157.1 (1_1), MP205.1 (1_1), MP253.1 (1_1), MP301.1 (1_1), MP349.1 (1_1), MP397.1 (1_1), MP445.1 (1_1), MP493.1 (1_1), MP541.1 (1_1), MP589.1 (1_1), MP637.1 (1_1), MP685.1 (1_1), MP781.1 (1_1), U8.17 (Y4), U19.17 (Y4), U34.17 (Y4), U38.17 (Y4)
/Sector1/MP2_5: MP14.1 (1_1), MP14#2.1 (1_1), MP110.1 (1_1), MP158.1 (1_1), MP206.1 (1_1), MP254.1 (1_1), MP302.1 (1_1), MP350.1 (1_1), MP398.1 (1_1), MP446.1 (1_1), MP494.1 (1_1), MP542.1 (1_1), MP590.1 (1_1), MP638.1 (1_1), MP686.1 (1_1), MP782.1 (1_1), U8.15 (Y5), U19.15 (Y5), U34.15 (Y5), U38.15 (Y5)
/Sector1/MP2_6: MP15.1 (1_1), MP15#2.1 (1_1), MP111.1 (1_1), MP159.1 (1_1), MP207.1 (1_1), MP255.1 (1_1), MP303.1 (1_1), MP351.1 (1_1), MP399.1 (1_1), MP447.1 (1_1), MP495.1 (1_1), MP543.1 (1_1), MP591.1 (1_1), MP639.1 (1_1), MP687.1 (1_1), MP783.1 (1_1), U8.13 (Y6), U19.13 (Y6), U34.13 (Y6), U38.13 (Y6)
/Sector1/MP2_7: MP16.1 (1_1), MP16#2.1 (1_1), MP112.1 (1_1), MP160.1 (1_1), MP208.1 (1_1), MP256.1 (1_1), MP304.1 (1_1), MP352.1 (1_1), MP400.1 (1_1), MP448.1 (1_1), MP496.1 (1_1), MP544.1 (1_1), MP592.1 (1_1), MP640.1 (1_1), MP688.1 (1_1), MP784.1 (1_1), U8.11 (Y7), U19.11 (Y7), U34.11 (Y7), U38.11 (Y7)
/Sector1/MP3_0: MP17.1 (1_1), MP17#2.1 (1_1), MP113.1 (1_1), MP161.1 (1_1), MP209.1 (1_1), MP257.1 (1_1), MP305.1 (1_1), MP353.1 (1_1), MP401.1 (1_1), MP449.1 (1_1), MP497.1 (1_1), MP545.1 (1_1), MP593.1 (1_1), MP641.1 (1_1), MP689.1 (1_1), MP785.1 (1_1), U11.33 (Y0), U20.33 (Y0), U35.33 (Y0), U39.33 (Y0)
/Sector1/MP3_1: MP18.1 (1_1), MP18#2.1 (1_1), MP114.1 (1_1), MP162.1 (1_1), MP210.1 (1_1), MP258.1 (1_1), MP306.1 (1_1), MP354.1 (1_1), MP402.1 (1_1), MP450.1 (1_1), MP498.1 (1_1), MP546.1 (1_1), MP594.1 (1_1), MP642.1 (1_1), MP690.1 (1_1), MP786.1 (1_1), U11.35 (Y1), U20.35 (Y1), U35.35 (Y1), U39.35 (Y1)
/Sector1/MP3_2: MP19.1 (1_1), MP19#2.1 (1_1), MP115.1 (1_1), MP163.1 (1_1), MP211.1 (1_1), MP259.1 (1_1), MP307.1 (1_1), MP355.1 (1_1), MP403.1 (1_1), MP451.1 (1_1), MP499.1 (1_1), MP547.1 (1_1), MP595.1 (1_1), MP643.1 (1_1), MP691.1 (1_1), MP787.1 (1_1), U11.37 (Y2), U20.37 (Y2), U35.37 (Y2), U39.37 (Y2)
/Sector1/MP3_3: MP20.1 (1_1), MP20#2.1 (1_1), MP116.1 (1_1), MP164.1 (1_1), MP212.1 (1_1), MP260.1 (1_1), MP308.1 (1_1), MP356.1 (1_1), MP404.1 (1_1), MP452.1 (1_1), MP500.1 (1_1), MP548.1 (1_1), MP596.1 (1_1), MP644.1 (1_1), MP692.1 (1_1), MP788.1 (1_1), U11.39 (Y3), U20.39 (Y3), U35.39 (Y3), U39.39 (Y3)
/Sector1/MP3_4: MP21.1 (1_1), MP21#2.1 (1_1), MP117.1 (1_1), MP165.1 (1_1), MP213.1 (1_1), MP261.1 (1_1), MP309.1 (1_1), MP357.1 (1_1), MP405.1 (1_1), MP453.1 (1_1), MP501.1 (1_1), MP549.1 (1_1), MP597.1 (1_1), MP645.1 (1_1), MP693.1 (1_1), MP789.1 (1_1), U11.17 (Y4), U20.17 (Y4), U35.17 (Y4), U39.17 (Y4)
/Sector1/MP3_5: MP22.1 (1_1), MP22#2.1 (1_1), MP118.1 (1_1), MP166.1 (1_1), MP214.1 (1_1), MP262.1 (1_1), MP310.1 (1_1), MP358.1 (1_1), MP406.1 (1_1), MP454.1 (1_1), MP502.1 (1_1), MP550.1 (1_1), MP598.1 (1_1), MP646.1 (1_1), MP694.1 (1_1), MP790.1 (1_1), U11.15 (Y5), U20.15 (Y5), U35.15 (Y5), U39.15 (Y5)
/Sector1/MP3_6: MP23.1 (1_1), MP23#2.1 (1_1), MP119.1 (1_1), MP167.1 (1_1), MP215.1 (1_1), MP263.1 (1_1), MP311.1 (1_1), MP359.1 (1_1), MP407.1 (1_1), MP455.1 (1_1), MP503.1 (1_1), MP551.1 (1_1), MP599.1 (1_1), MP647.1 (1_1), MP695.1 (1_1), MP791.1 (1_1), U11.13 (Y6), U20.13 (Y6), U35.13 (Y6), U39.13 (Y6)
/Sector1/MP3_7: MP24.1 (1_1), MP24#2.1 (1_1), MP120.1 (1_1), MP168.1 (1_1), MP216.1 (1_1), MP264.1 (1_1), MP312.1 (1_1), MP360.1 (1_1), MP408.1 (1_1), MP456.1 (1_1), MP504.1 (1_1), MP552.1 (1_1), MP600.1 (1_1), MP648.1 (1_1), MP696.1 (1_1), MP792.1 (1_1), U11.11 (Y7), U20.11 (Y7), U35.11 (Y7), U39.11 (Y7)
/Sector1/MP4_0: MP25.1 (1_1), MP25#2.1 (1_1), MP121.1 (1_1), MP169.1 (1_1), MP217.1 (1_1), MP265.1 (1_1), MP313.1 (1_1), MP361.1 (1_1), MP409.1 (1_1), MP457.1 (1_1), MP505.1 (1_1), MP553.1 (1_1), MP601.1 (1_1), MP649.1 (1_1), MP697.1 (1_1), MP793.1 (1_1), U12.33 (Y0), U21.33 (Y0), U36.33 (Y0), U40.33 (Y0)
/Sector1/MP4_1: MP26.1 (1_1), MP26#2.1 (1_1), MP122.1 (1_1), MP170.1 (1_1), MP218.1 (1_1), MP266.1 (1_1), MP314.1 (1_1), MP362.1 (1_1), MP410.1 (1_1), MP458.1 (1_1), MP506.1 (1_1), MP554.1 (1_1), MP602.1 (1_1), MP650.1 (1_1), MP698.1 (1_1), MP794.1 (1_1), U12.35 (Y1), U21.35 (Y1), U36.35 (Y1), U40.35 (Y1)
/Sector1/MP4_2: MP27.1 (1_1), MP27#2.1 (1_1), MP123.1 (1_1), MP171.1 (1_1), MP219.1 (1_1), MP267.1 (1_1), MP315.1 (1_1), MP363.1 (1_1), MP411.1 (1_1), MP459.1 (1_1), MP507.1 (1_1), MP555.1 (1_1), MP603.1 (1_1), MP651.1 (1_1), MP699.1 (1_1), MP795.1 (1_1), U12.37 (Y2), U21.37 (Y2), U36.37 (Y2), U40.37 (Y2)
/Sector1/MP4_3: MP28.1 (1_1), MP28#2.1 (1_1), MP124.1 (1_1), MP172.1 (1_1), MP220.1 (1_1), MP268.1 (1_1), MP316.1 (1_1), MP364.1 (1_1), MP412.1 (1_1), MP460.1 (1_1), MP508.1 (1_1), MP556.1 (1_1), MP604.1 (1_1), MP652.1 (1_1), MP700.1 (1_1), MP796.1 (1_1), U12.39 (Y3), U21.39 (Y3), U36.39 (Y3), U40.39 (Y3)
/Sector1/MP4_4: MP29.1 (1_1), MP29#2.1 (1_1), MP125.1 (1_1), MP173.1 (1_1), MP221.1 (1_1), MP269.1 (1_1), MP317.1 (1_1), MP365.1 (1_1), MP413.1 (1_1), MP461.1 (1_1), MP509.1 (1_1), MP557.1 (1_1), MP605.1 (1_1), MP653.1 (1_1), MP701.1 (1_1), MP797.1 (1_1), U12.17 (Y4), U21.17 (Y4), U36.17 (Y4), U40.17 (Y4)
/Sector1/MP4_5: MP30.1 (1_1), MP30#2.1 (1_1), MP126.1 (1_1), MP174.1 (1_1), MP222.1 (1_1), MP270.1 (1_1), MP318.1 (1_1), MP366.1 (1_1), MP414.1 (1_1), MP462.1 (1_1), MP510.1 (1_1), MP558.1 (1_1), MP606.1 (1_1), MP654.1 (1_1), MP702.1 (1_1), MP798.1 (1_1), U12.15 (Y5), U21.15 (Y5), U36.15 (Y5), U40.15 (Y5)
/Sector1/MP4_6: MP31.1 (1_1), MP31#2.1 (1_1), MP127.1 (1_1), MP175.1 (1_1), MP223.1 (1_1), MP271.1 (1_1), MP319.1 (1_1), MP367.1 (1_1), MP415.1 (1_1), MP463.1 (1_1), MP511.1 (1_1), MP559.1 (1_1), MP607.1 (1_1), MP655.1 (1_1), MP703.1 (1_1), MP799.1 (1_1), U12.13 (Y6), U21.13 (Y6), U36.13 (Y6), U40.13 (Y6)
/Sector1/MP4_7: MP32.1 (1_1), MP32#2.1 (1_1), MP128.1 (1_1), MP176.1 (1_1), MP224.1 (1_1), MP272.1 (1_1), MP320.1 (1_1), MP368.1 (1_1), MP416.1 (1_1), MP464.1 (1_1), MP512.1 (1_1), MP560.1 (1_1), MP608.1 (1_1), MP656.1 (1_1), MP704.1 (1_1), MP800.1 (1_1), U12.11 (Y7), U21.11 (Y7), U36.11 (Y7), U40.11 (Y7)
/Sector1/RST: C14.2, D1.2 (A), SMR1.2, U8.41 (RST), U11.41 (RST), U12.41 (RST), U18.41 (RST), U19.41 (RST), U20.41 (RST), U21.41 (RST), U33.41 (RST), U34.41 (RST), U35.41 (RST), U36.41 (RST), U37.41 (RST), U38.41 (RST), U39.41 (RST), U40.41 (RST), U57.41 (RST)
/Sector1/STROBE1: R35.1, U5.17 (GPA0), U57.14 (STB)
/Sector1/STROBE2: R36.1, U5.18 (GPA1), U8.14 (STB)
/Sector1/STROBE3: R37.1, U5.19 (GPA2), U11.14 (STB)
/Sector1/STROBE4: R38.1, U5.20 (GPA3), U12.14 (STB)
/Sector1/STROBE5: R39.1, U5.21 (GPA4), U18.14 (STB)
/Sector1/STROBE6: R40.1, U5.22 (GPA5), U19.14 (STB)
/Sector1/STROBE7: R41.1, U5.23 (GPA6), U20.14 (STB)
/Sector1/STROBE8: R42.1, U5.24 (GPA7), U21.14 (STB)
/Sector1/STROBE9: R43.1, U5.25 (GPB0), U33.14 (STB)
/Sector1/STROBE10: R44.1, U5.26 (GPB1), U34.14 (STB)
/Sector1/STROBE11: R45.1, U5.27 (GPB2), U35.14 (STB)
/Sector1/STROBE12: R46.1, U5.28 (GPB3), U36.14 (STB)
/Sector1/STROBE13: R47.1, U5.1 (GPB4), U37.14 (STB)
/Sector1/STROBE14: R48.1, U5.2 (GPB5), U38.14 (STB)
/Sector1/STROBE15: R49.1, U5.3 (GPB6), U39.14 (STB)
/Sector1/STROBE16: R50.1, U5.4 (GPB7), U40.14 (STB)
/Sector2/CLK: R51.2, U9.34 (CS/CK), U10.34 (CS/CK), U13.34 (CS/CK), U14.34 (CS/CK), U15.34 (CS/CK), U16.34 (CS/CK), U17.34 (CS/CK), U22.34 (CS/CK), U23.34 (CS/CK), U24.34 (CS/CK), U25.34 (CS/CK), U26.34 (CS/CK), U27.34 (CS/CK), U28.34 (CS/CK), U29.34 (CS/CK), U30.34 (CS/CK)
/Sector2/DAT: R52.2, U9.36 (DAT), U10.36 (DAT), U13.36 (DAT), U14.36 (DAT), U15.36 (DAT), U16.36 (DAT), U17.36 (DAT), U22.36 (DAT), U23.36 (DAT), U24.36 (DAT), U25.36 (DAT), U26.36 (DAT), U27.36 (DAT), U28.36 (DAT), U29.36 (DAT), U30.36 (DAT)
/Sector2/MP1_0: MP33.1 (1_1), MP33#2.1 (1_1), MP129.1 (1_1), MP177.1 (1_1), MP225.1 (1_1), MP273.1 (1_1), MP321.1 (1_1), MP369.1 (1_1), MP417.1 (1_1), MP465.1 (1_1), MP513.1 (1_1), MP561.1 (1_1), MP609.1 (1_1), MP657.1 (1_1), MP705.1 (1_1), MP801.1 (1_1), U17.33 (Y0), U22.33 (Y0), U23.33 (Y0), U28.33 (Y0)
/Sector2/MP1_1: MP34.1 (1_1), MP34#2.1 (1_1), MP130.1 (1_1), MP178.1 (1_1), MP226.1 (1_1), MP274.1 (1_1), MP322.1 (1_1), MP370.1 (1_1), MP418.1 (1_1), MP466.1 (1_1), MP514.1 (1_1), MP562.1 (1_1), MP610.1 (1_1), MP658.1 (1_1), MP706.1 (1_1), MP802.1 (1_1), U17.35 (Y1), U22.35 (Y1), U23.35 (Y1), U28.35 (Y1)
/Sector2/MP1_2: MP35.1 (1_1), MP35#2.1 (1_1), MP131.1 (1_1), MP179.1 (1_1), MP227.1 (1_1), MP275.1 (1_1), MP323.1 (1_1), MP371.1 (1_1), MP419.1 (1_1), MP467.1 (1_1), MP515.1 (1_1), MP563.1 (1_1), MP611.1 (1_1), MP659.1 (1_1), MP707.1 (1_1), MP803.1 (1_1), U17.37 (Y2), U22.37 (Y2), U23.37 (Y2), U28.37 (Y2)
/Sector2/MP1_3: MP36.1 (1_1), MP36#2.1 (1_1), MP132.1 (1_1), MP180.1 (1_1), MP228.1 (1_1), MP276.1 (1_1), MP324.1 (1_1), MP372.1 (1_1), MP420.1 (1_1), MP468.1 (1_1), MP516.1 (1_1), MP564.1 (1_1), MP612.1 (1_1), MP660.1 (1_1), MP708.1 (1_1), MP804.1 (1_1), U17.39 (Y3), U22.39 (Y3), U23.39 (Y3), U28.39 (Y3)
/Sector2/MP1_4: MP37.1 (1_1), MP37#2.1 (1_1), MP133.1 (1_1), MP181.1 (1_1), MP229.1 (1_1), MP277.1 (1_1), MP325.1 (1_1), MP373.1 (1_1), MP421.1 (1_1), MP469.1 (1_1), MP517.1 (1_1), MP565.1 (1_1), MP613.1 (1_1), MP661.1 (1_1), MP709.1 (1_1), MP805.1 (1_1), U17.17 (Y4), U22.17 (Y4), U23.17 (Y4), U28.17 (Y4)
/Sector2/MP1_5: MP38.1 (1_1), MP38#2.1 (1_1), MP134.1 (1_1), MP182.1 (1_1), MP230.1 (1_1), MP278.1 (1_1), MP326.1 (1_1), MP374.1 (1_1), MP422.1 (1_1), MP470.1 (1_1), MP518.1 (1_1), MP566.1 (1_1), MP614.1 (1_1), MP662.1 (1_1), MP710.1 (1_1), MP806.1 (1_1), U17.15 (Y5), U22.15 (Y5), U23.15 (Y5), U28.15 (Y5)
/Sector2/MP1_6: MP39.1 (1_1), MP39#2.1 (1_1), MP135.1 (1_1), MP183.1 (1_1), MP231.1 (1_1), MP279.1 (1_1), MP327.1 (1_1), MP375.1 (1_1), MP423.1 (1_1), MP471.1 (1_1), MP519.1 (1_1), MP567.1 (1_1), MP615.1 (1_1), MP663.1 (1_1), MP711.1 (1_1), MP807.1 (1_1), U17.13 (Y6), U22.13 (Y6), U23.13 (Y6), U28.13 (Y6)
/Sector2/MP1_7: MP40.1 (1_1), MP40#2.1 (1_1), MP136.1 (1_1), MP184.1 (1_1), MP232.1 (1_1), MP280.1 (1_1), MP328.1 (1_1), MP376.1 (1_1), MP424.1 (1_1), MP472.1 (1_1), MP520.1 (1_1), MP568.1 (1_1), MP616.1 (1_1), MP664.1 (1_1), MP712.1 (1_1), MP808.1 (1_1), U17.11 (Y7), U22.11 (Y7), U23.11 (Y7), U28.11 (Y7)
/Sector2/MP2_0: MP41.1 (1_1), MP41#2.1 (1_1), MP137.1 (1_1), MP185.1 (1_1), MP233.1 (1_1), MP281.1 (1_1), MP329.1 (1_1), MP377.1 (1_1), MP425.1 (1_1), MP473.1 (1_1), MP521.1 (1_1), MP569.1 (1_1), MP617.1 (1_1), MP665.1 (1_1), MP713.1 (1_1), MP809.1 (1_1), U10.33 (Y0), U14.33 (Y0), U15.33 (Y0), U29.33 (Y0)
/Sector2/MP2_1: MP42.1 (1_1), MP42#2.1 (1_1), MP138.1 (1_1), MP186.1 (1_1), MP234.1 (1_1), MP282.1 (1_1), MP330.1 (1_1), MP378.1 (1_1), MP426.1 (1_1), MP474.1 (1_1), MP522.1 (1_1), MP570.1 (1_1), MP618.1 (1_1), MP666.1 (1_1), MP714.1 (1_1), MP810.1 (1_1), U10.35 (Y1), U14.35 (Y1), U15.35 (Y1), U29.35 (Y1)
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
